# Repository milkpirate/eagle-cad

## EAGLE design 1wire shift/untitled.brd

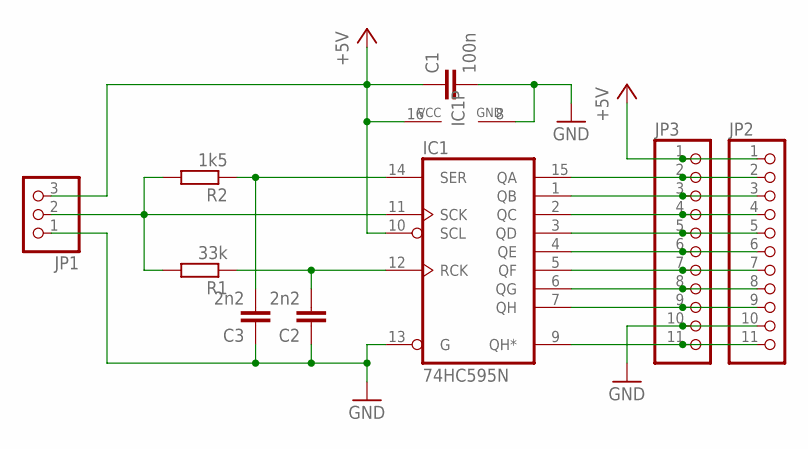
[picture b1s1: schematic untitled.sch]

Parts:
C1: 100n; C025-025X050
C2, C3: 2n2; C025-025X050
IC1: 74HC595N; DIL16
JP1: PINHD-1X3; 1X03
JP2, JP3: PINHD-1X11; 1X11
R1: 33k; 0204/7
R2: 1k5; 0204/7

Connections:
+5V: C1.1, IC1.10 (SCL), IC1.16 (VCC), JP1.3, JP2.1, JP3.1
GND: C1.2, C2.1, C3.1, IC1.8 (GND), IC1.13 (G), JP1.1, JP2.10, JP3.10
unnamed: IC1.15 (QA), JP2.2, JP3.2
unnamed: IC1.1 (QB), JP2.3, JP3.3
unnamed: IC1.2 (QC), JP2.4, JP3.4
unnamed: C3.2, IC1.14 (SER), R2.1
unnamed: IC1.3 (QD), JP2.5, JP3.5
unnamed: C2.2, IC1.12 (RCK), R1.1
unnamed: IC1.4 (QE), JP2.6, JP3.6
unnamed: IC1.11 (SCK), JP1.2, R1.2, R2.2
unnamed: IC1.5 (QF), JP2.7, JP3.7
unnamed: IC1.6 (QG), JP2.8, JP3.8
unnamed: IC1.7 (QH), JP2.9, JP3.9
unnamed: IC1.9 (QH*), JP2.11, JP3.11

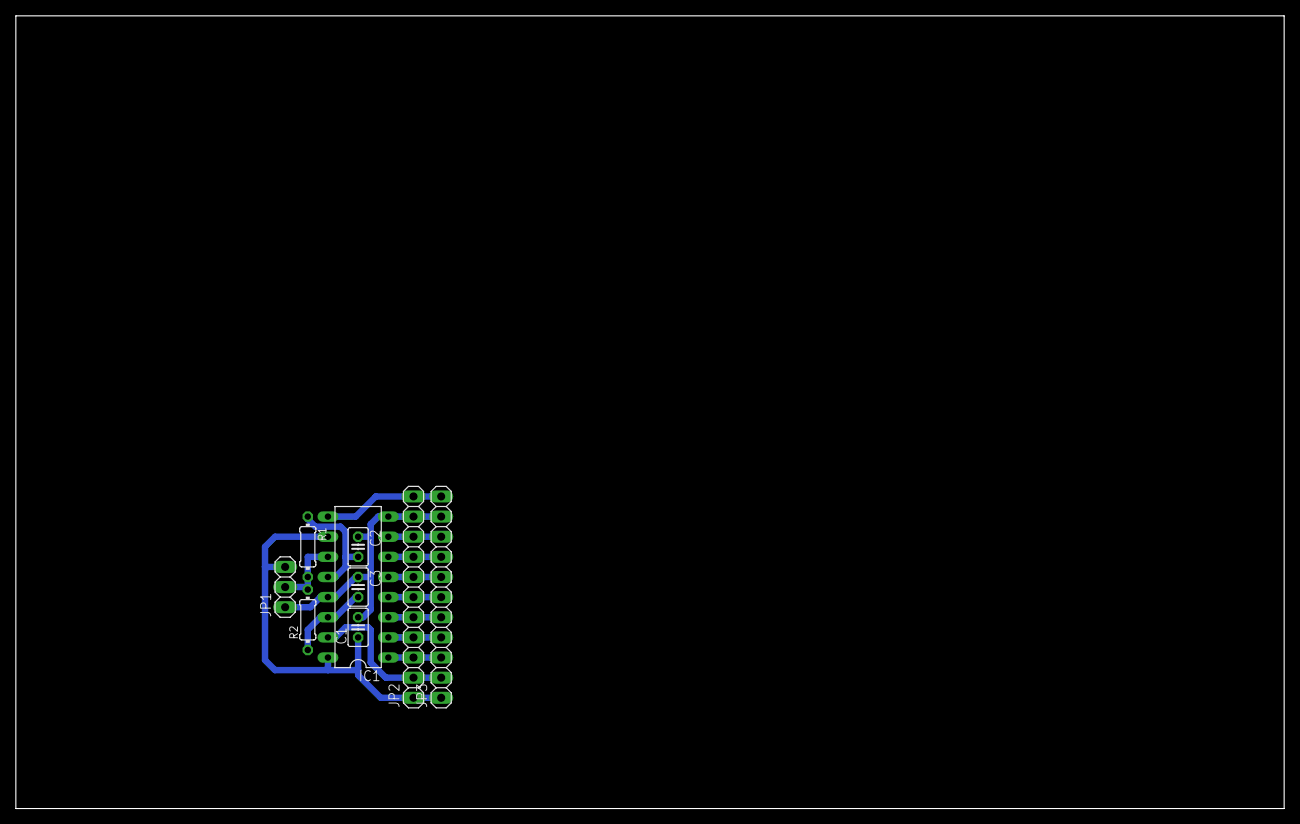
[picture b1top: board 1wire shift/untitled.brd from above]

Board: 2 copper layers, 160.0 x 100.0 mm, 9 parts (0 on the bottom side), 14 nets.

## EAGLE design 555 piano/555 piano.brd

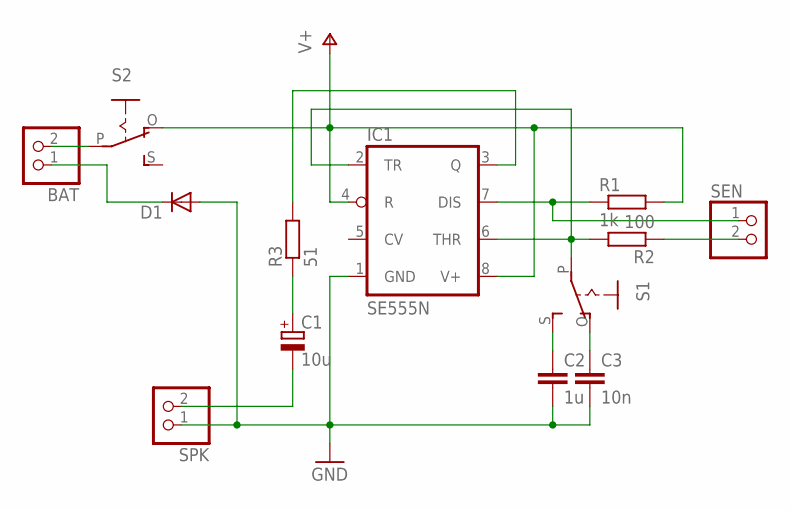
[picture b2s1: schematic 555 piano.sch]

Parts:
BAT: PINHD-1X2; 1X02
C1: 10u; TT2D5L
C2: 1u; C025-025X050
C3: 10n; C025-025X050
D1: DIODE-D-5; D-5
IC1: SE555N; DIL08-ROUND
R1: 1k; 0204/7
R2: 100; 0204/7
R3: 51; 0204/7
S1, S2: EG1218S; EG1218
SEN: PINHD-1X2; 1X02
SPK: PINHD-1X2; 1X02

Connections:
GND: C2.2, C3.2, D1.A, IC1.1 (GND), SPK.1
unnamed: C1.-, SPK.2
unnamed: IC1.7 (DIS), R1.1, SEN.1
unnamed: IC1.3 (Q), R3.2
unnamed: C1.+, R3.1
unnamed: R2.1, SEN.2
unnamed: IC1.2 (TR), IC1.6 (THR), R2.2, S1.P
unnamed: C2.1, S1.S
unnamed: C3.1, S1.O
unnamed: BAT.1, D1.C
unnamed: BAT.2, S2.P
V+: IC1.4 (R), IC1.8 (V+), R1.2, S2.O

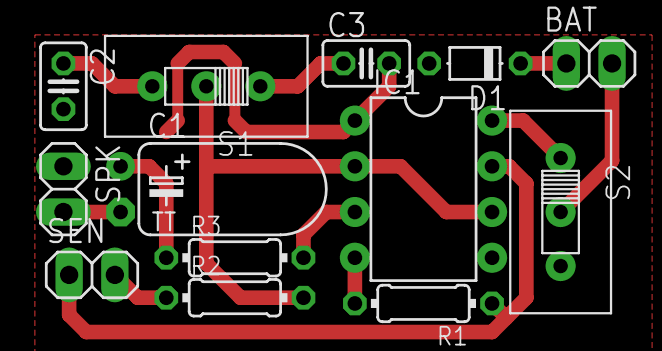
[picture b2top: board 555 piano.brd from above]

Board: 2 copper layers, 13 parts (0 on the bottom side), 12 nets.

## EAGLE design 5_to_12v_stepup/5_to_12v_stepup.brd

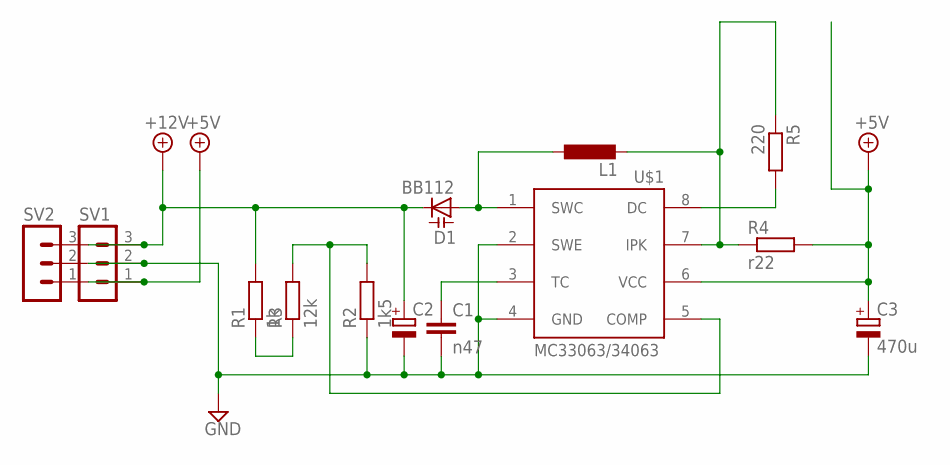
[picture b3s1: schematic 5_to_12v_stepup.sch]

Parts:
C1: n47; C025-025X050
C2: CPOL-EUE3.5-8; E3,5-8
C3: 470u; E3,5-8
D1: BB112; SOT54H
L1: L-EU0207/2V; 0207/2V
R1: 1k; 0207/2V
R2: 1k5; 0207/2V
R3: 12k; 0207/2V
R4: r22; 0207/2V
R5: 220; 0207/2V
SV1, SV2: MA03-1
U$1: MC33063/MC34063P; DIL08

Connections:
+5V: C3.+, R4.2, SV1.1, SV2.1, U$1.6 (VCC)
+12V: C2.+, D1.C, R1.2, SV1.3, SV2.3
GND: C1.2, C2.-, C3.-, R2.1, SV1.2, SV2.2, U$1.2 (SWE), U$1.4 (GND)
unnamed: R5.2, U$1.8 (DC)
unnamed: L1.2, R4.1, R5.1, U$1.7 (IPK)
unnamed: R1.1, R3.1
unnamed: C1.1, U$1.3 (TC)
unnamed: D1.A, L1.1, U$1.1 (SWC)
unnamed: R2.2, R3.2, U$1.5 (COMP)

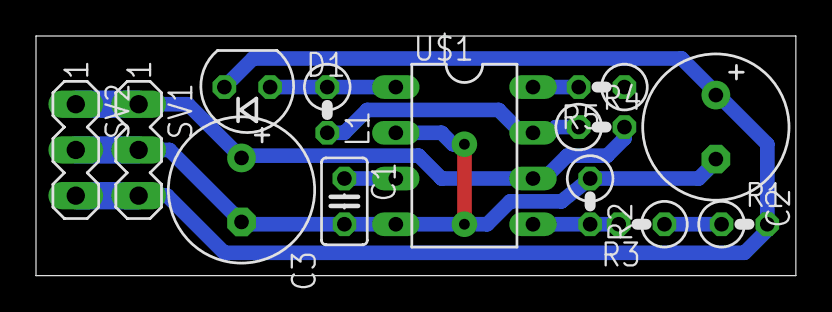
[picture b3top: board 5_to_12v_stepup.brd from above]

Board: 2 copper layers, 42.2 x 13.3 mm, 13 parts (0 on the bottom side), 9 nets.

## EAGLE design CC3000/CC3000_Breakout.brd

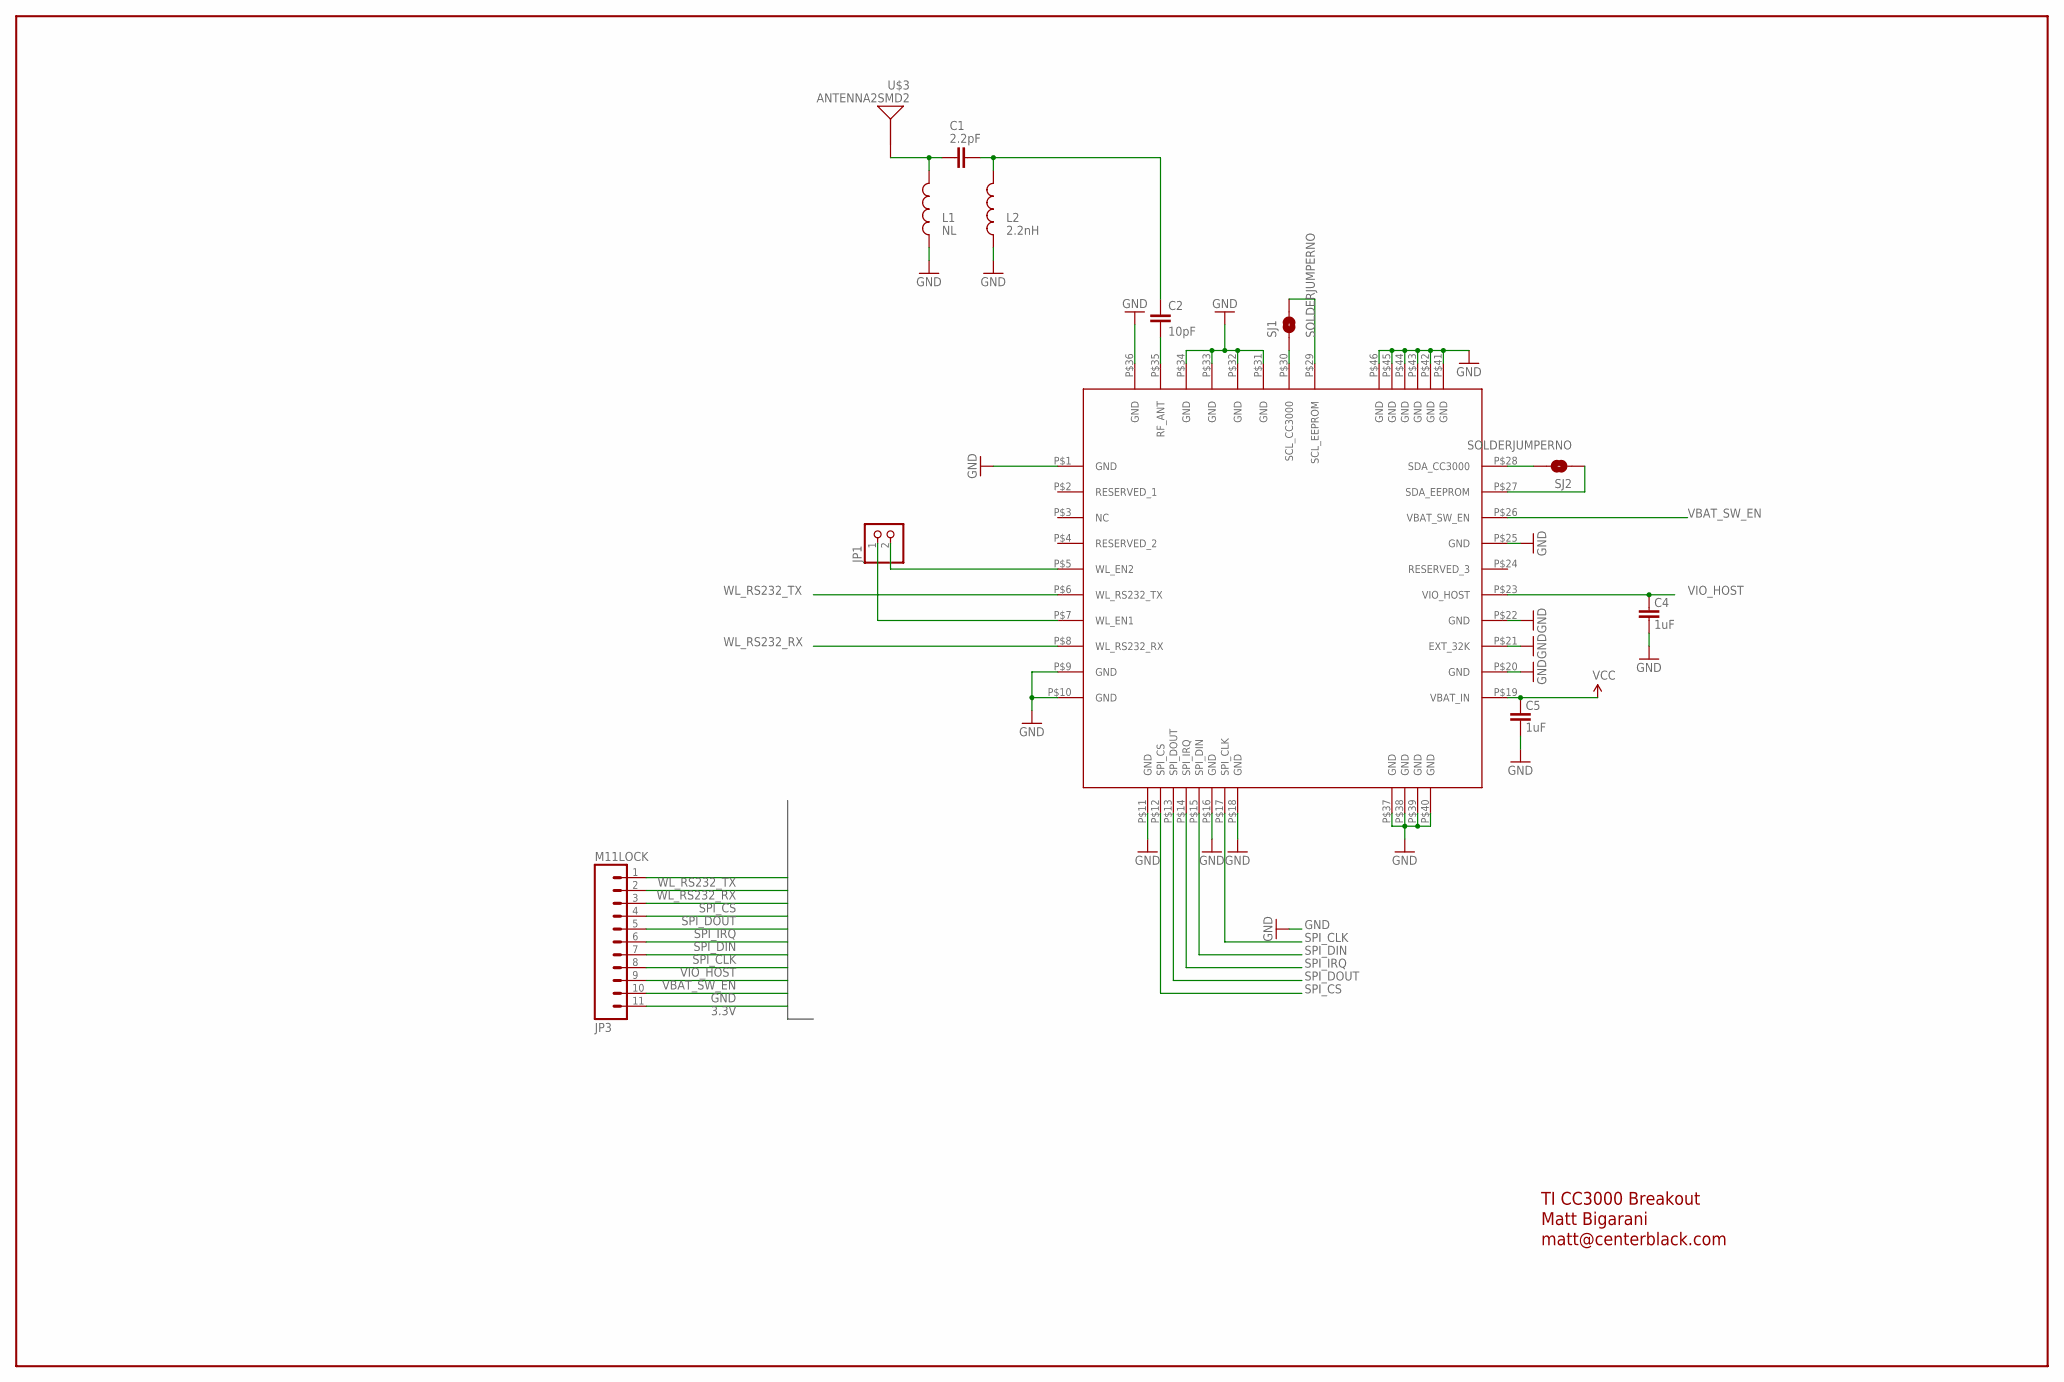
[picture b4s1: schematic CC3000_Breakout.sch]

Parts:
C1: 2.2pF; 0805
C2: 10pF; 0805
C4, C5: 1uF; 0805
JP1: PINHD-1X2; 1X02
JP3: M11LOCK; 1X11_LOCK
L1: NL; 0805
L2: 2.2nH; 0805
SJ1, SJ2: SOLDERJUMPERNO; SJ_2S-NO
U$1: CC3000
U$3: ANTENNA2SMD2; ANTENNA-CHIP3

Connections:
3.3V: C5.2, JP3.11, U$1.P$19 (VBAT_IN)
GND: C4.1, C5.1, JP3.10, L1.1, L2.1, U$1.P$1 (GND), U$1.P$9 (GND), U$1.P$10 (GND), U$1.P$11 (GND), U$1.P$16 (GND), U$1.P$18 (GND), U$1.P$20 (GND), U$1.P$21 (EXT_32K), U$1.P$22 (GND), U$1.P$25 (GND), U$1.P$31 (GND), U$1.P$32 (GND), U$1.P$33 (GND), U$1.P$34 (GND), U$1.P$36 (GND), U$1.P$37 (GND), U$1.P$38 (GND), U$1.P$39 (GND), U$1.P$40 (GND), U$1.P$41 (GND), U$1.P$42 (GND), U$1.P$43 (GND), U$1.P$44 (GND), U$1.P$45 (GND), U$1.P$46 (GND)
unnamed: C1.2, C2.1, L2.2
unnamed: C2.2, U$1.P$35 (RF_ANT)
unnamed: SJ1.1, U$1.P$30 (SCL_CC3000)
unnamed: C1.1, L1.2, U$3.FEED
unnamed: SJ1.2, U$1.P$29 (SCL_EEPROM)
unnamed: SJ2.2, U$1.P$28 (SDA_CC3000)
unnamed: SJ2.1, U$1.P$27 (SDA_EEPROM)
SPI_CLK: JP3.7, U$1.P$17 (SPI_CLK)
SPI_CS: JP3.3, U$1.P$12 (SPI_CS)
SPI_DIN: JP3.6, U$1.P$15 (SPI_DIN)
SPI_DOUT: JP3.4, U$1.P$13 (SPI_DOUT)
SPI_IRQ: JP3.5, U$1.P$14 (SPI_IRQ)
VBAT_SW_EN: JP3.9, U$1.P$26 (VBAT_SW_EN)
VIO_HOST: C4.2, JP3.8, U$1.P$23 (VIO_HOST)
WL_EN1: JP1.1, U$1.P$7 (WL_EN1)
WL_EN2: JP1.2, U$1.P$5 (WL_EN2)
WL_RS232_RX: JP3.2, U$1.P$8 (WL_RS232_RX)
WL_RS232_TX: JP3.1, U$1.P$6 (WL_RS232_TX)

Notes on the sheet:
Matt Bigarani
matt@centerblack.com
TI CC3000 Breakout

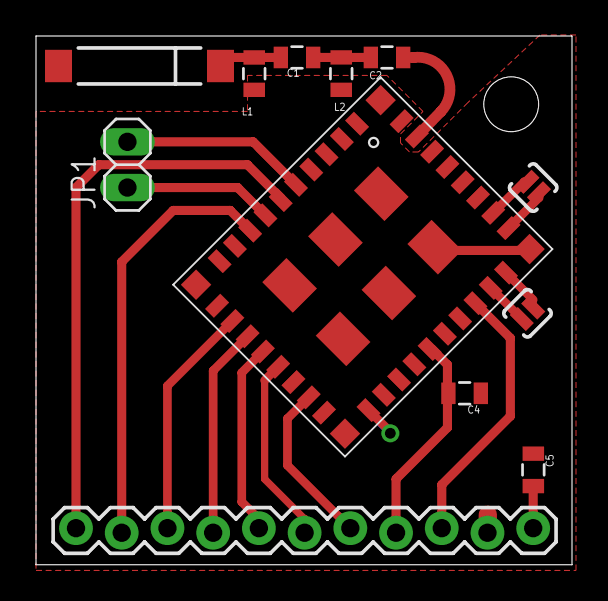
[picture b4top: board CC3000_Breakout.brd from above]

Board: 2 copper layers, 29.8 x 29.4 mm, 13 parts (0 on the bottom side), 20 nets.

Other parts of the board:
U$2: STAND-OFF-TIGHT

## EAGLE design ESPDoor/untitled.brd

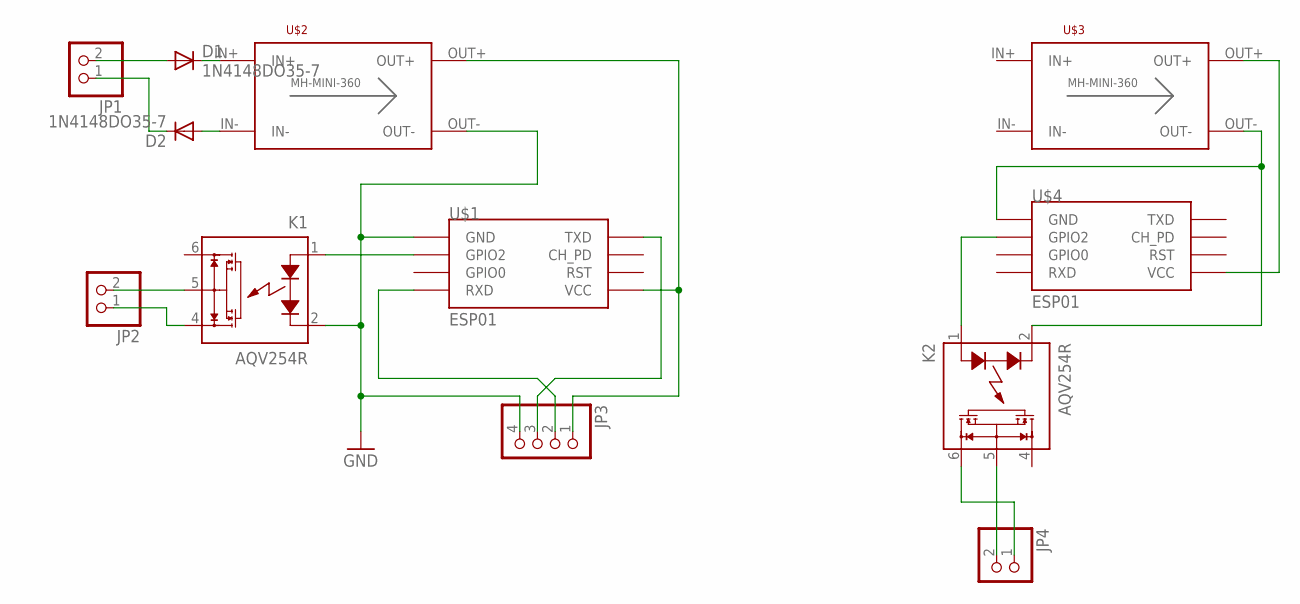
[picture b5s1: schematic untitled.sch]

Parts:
D1, D2: 1N4148DO35-7; DO35-7
JP1, JP2, JP4: PINHD-1X2; 1X02
JP3: PINHD-1X4; 1X04
K1: AQV254R; DIL06
K2: AQV254R; DIL06; MPN AQV254
U$1, U$4: ESP01
U$2, U$3: DC-DC_CONV_MINISTD; DC-DC_CONV_MINI

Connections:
GND: JP3.4, K1.2 (K), U$1.GND, U$2.OUT-
unnamed: D1.C, U$2.IN+
unnamed: D2.A, U$2.IN-
unnamed: JP2.2, K1.5 (S)
unnamed: JP3.1, U$1.VCC, U$2.OUT+
unnamed: K1.1 (A), U$1.GPIO2
unnamed: JP3.2, U$1.RX (RXD)
unnamed: JP3.3, U$1.TX (TXD)
unnamed: JP2.1, K1.4 (D2)
unnamed: D1.A, JP1.2
unnamed: D2.C, JP1.1
unnamed: K2.2 (K), U$3.OUT-, U$4.GND
unnamed: U$3.OUT+, U$4.VCC
unnamed: K2.1 (A), U$4.GPIO2
unnamed: JP4.2, K2.5 (S)
unnamed: JP4.1, K2.6 (D1)

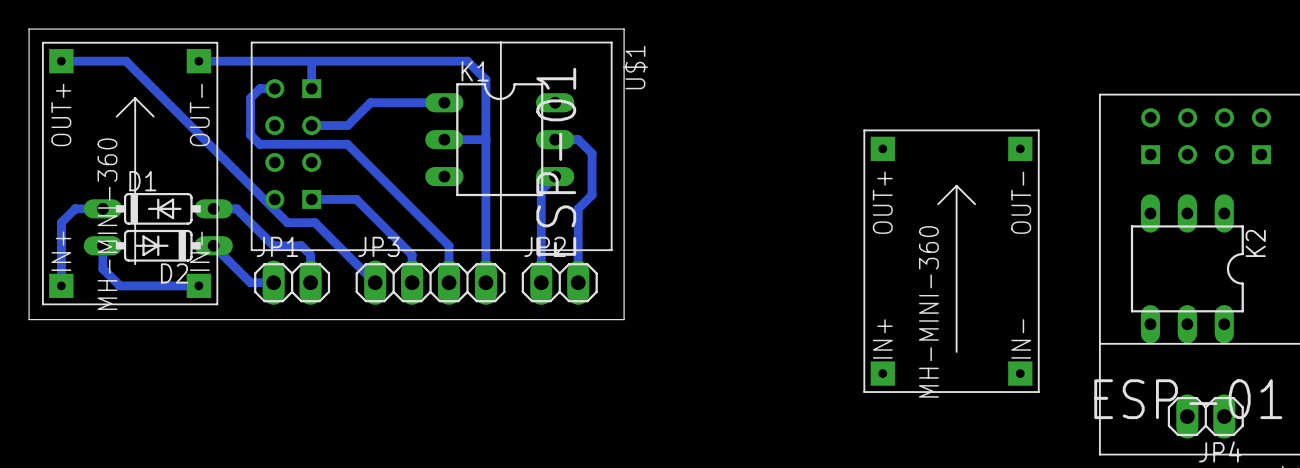
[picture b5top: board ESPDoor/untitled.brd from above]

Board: 2 copper layers, 40.9 x 20.0 mm, 12 parts (0 on the bottom side), 16 nets.
